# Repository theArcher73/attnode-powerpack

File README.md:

# AttNo.de-powerpack, a adapter-pcb to use 3.3-15V
 AddOn to use the [attnode](https://attno.de) v2/v3 with 3.3-15V DC

This small pcb allows to run the [attnode](https://attno.de) with an operating voltage between 3.3 and 15V, for example with a USB power supply, a LiPo or any other fixed voltage power supply.

It has the shape of the CR2032 battery clip and is soldered directly onto the [attnode](https://attno.de) instead of the CR2032-Clip.

Therefore, when ordering the pcb's, a smaller pcb thickness can be used if possible, I have had good experiences with 1.2mm.

The power supply can be either via the JST socket, or the two pads directly on the pcb. In this case, the JST socket must not be soldered.

The voltage source must provide at least 120 mA.

Update 26.05.2021: add a Voltage divider added to monitor the Vin with an ADC pin of the ATTiny. The resistance ratio must be determined based on Vin, here are some sample values. The voltage at the ADC pad should not exceed 2.1V.

Update 27.08.2021: add two Resistors 5K1 and Pads for external wiring to support USB-C

  Vin | Vmax |  R1 | R2
------|------|-----|----
3.7V | 4.2V | 1M | 1M
USB | 5.25V | 1M5 | 1M
9V | 11V | 6M8 | 1M5
12V | 15.4V | 10M | 1M5

Attention! Pay attention to the peak voltage, which is higher than the nominal voltage for many batteries!

More information can be found [here](https://www.attno.de/blog/2021-01-08).

 front  | back       
--------|--------
 | 

## Disclaimer

The documentation of the attno.de-powerpack is distributed in the hope that it will be useful, but WITHOUT ANY WARRANTY; without even the implied warranty of MERCHANTABILITY or FITNESS FOR A PARTICULAR PURPOSE.

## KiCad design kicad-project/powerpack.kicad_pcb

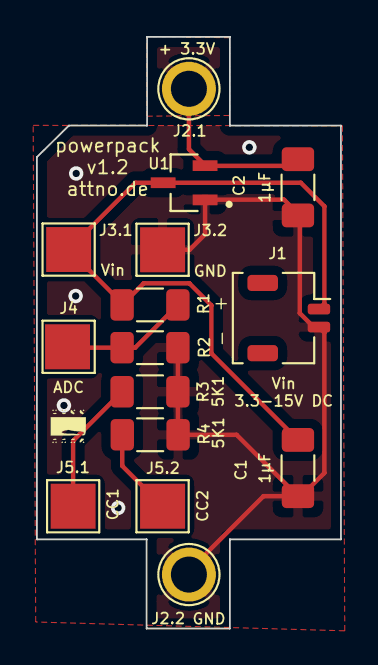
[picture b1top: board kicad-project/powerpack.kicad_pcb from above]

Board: 2 copper layers, 16.9 x 32.9 mm, 15 parts (0 on the bottom side), 6 nets.

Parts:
C1, C2: 1µF; C_1206_3216Metric_Pad1.33x1.80mm_HandSolder
J1: Power_in 3.3-15V; JST_SHL_SM02B-SHLS-TF_1x02-1MP_P1.00mm_Horizontal
J2.1: Vout +3.3V; TestPoint_Plated_Hole_D2.0mm
J2.2: Vout GND; TestPoint_Plated_Hole_D2.0mm
J3.1: Vin; TestPoint_Pad_2.5x2.5mm
J3.2: GND; TestPoint_Pad_2.5x2.5mm
J4: ADC; TestPoint_Pad_2.5x2.5mm
J5.1: CC1; TestPoint_Pad_2.5x2.5mm
J5.2: CC2; TestPoint_Pad_2.5x2.5mm
R1, R2: R; R_1206_3216Metric_Pad1.30x1.75mm_HandSolder
R3, R4: 5K1; R_1206_3216Metric_Pad1.30x1.75mm_HandSolder
U1: MCP1703T-3302E_CB; SOT95P255X145-3N

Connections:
+3V3: C2.1, J2.1.1, U1.2
GND: C1.2, C2.2, J1.2, J2.2.1, J3.2.1, R2.2, R3.2, R4.2, U1.1
unnamed: J4.1, R1.2, R2.1
unnamed: J5.1.1, R3.1
unnamed: J5.2.1, R4.1
VCC: C1.1, J1.1, J3.1.1, R1.1, U1.3

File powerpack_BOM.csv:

Reference;Quantity;Value;Bauteil;Footprint
C1, C2;2;1µF;Capacitor SMD 1206;Capacitor_SMD:C_1206_3216Metric_Pad1.33x1.80mm_HandSolder
J1;1;Power_in 3.3-15V;JST 2pin 1mm horizontal;Connector_JST:JST_SHL_SM02B-SHLS-TF_1x02-1MP_P1.00mm_Horizontal
U1;1;MCP1703T-3302E_CB;MCP 1703-3302E/CB;MCP1703T-3302E_CB:SOT95P255X145-3N

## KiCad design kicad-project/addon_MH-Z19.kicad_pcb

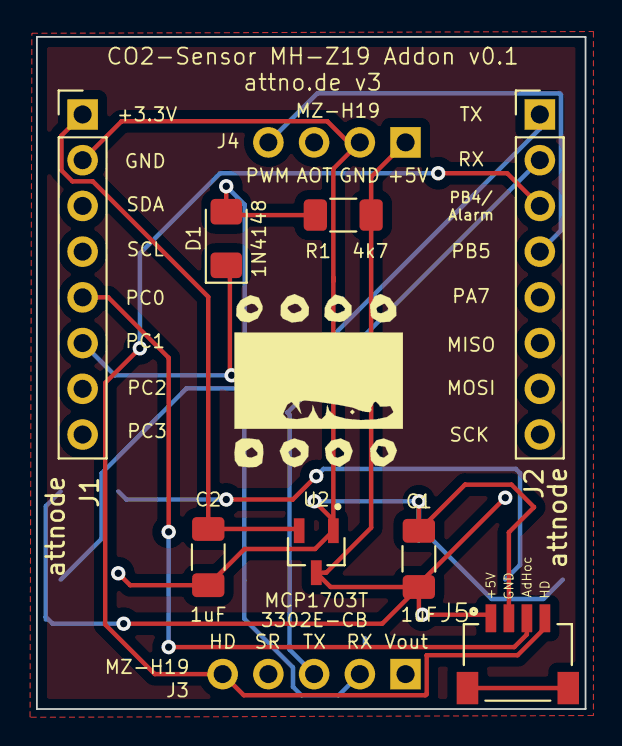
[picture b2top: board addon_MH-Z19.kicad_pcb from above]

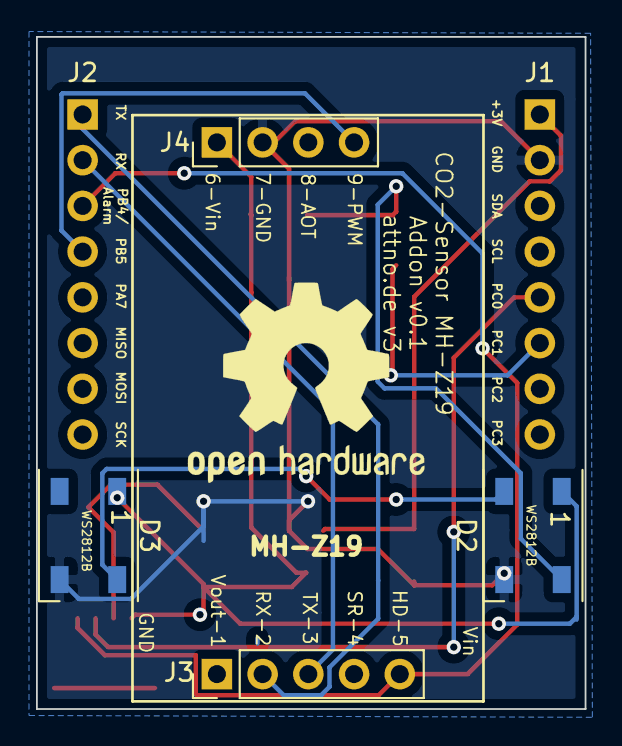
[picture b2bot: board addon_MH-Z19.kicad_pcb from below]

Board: 2 copper layers, 30.5 x 37.3 mm, 12 parts (4 on the bottom side), 12 nets.

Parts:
C1, C2: 1uF; C_1206_3216Metric_Pad1.33x1.80mm_HandSolder
D1: 1N4148; D_1206_3216Metric_Pad1.42x1.75mm_HandSolder
D2, D3: WS2812B; LED_WS2812B_PLCC4_5.0x5.0mm_P3.2mm
J1, J2: attnode; PinHeader_1x08_P2.54mm_Vertical
J3: MZ-H19; PinHeader_1x05_P2.54mm_Vertical
J4: MZ-H19; PinHeader_1x04_P2.54mm_Vertical
J5: SM04B-SRSS-TBT(LF)(SN); JST_SM04B-SRSS-TB(LF)(SN)
R1: 4k7; R_1206_3216Metric_Pad1.30x1.75mm_HandSolder
U2: MCP1703T; SOT95P255X145-3N

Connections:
+3V3: C2.1, J1.1, U2.2
+5V: C1.1, D2.1, D3.1, J4.1, J5.1, R1.1, U2.3
AdHoc: J1.5, J5.3
GND: C1.2, C2.2, D2.3, D3.3, J1.2, J4.2, J5.2, U2.1
HD: J2.3, J3.5, J5.4
unnamed: D1.2, D2.4, R1.2
unnamed: D2.2, D3.4
unnamed: J5.S1, J5.S2
PC1: D1.1, J1.6
PWM: J2.4, J4.4
RX: J2.2, J3.3
TX: J2.1, J3.2

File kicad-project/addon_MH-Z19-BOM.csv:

Reference;Quantity;Value;Description;Footprint
C1, C2;2;1µF;Capacitor SMD 1206;Capacitor_SMD:C_1206_3216Metric_Pad1.33x1.80mm_HandSolder
D1;1;1N4148;Diode SMD 1206;Diode_SMD:D_1206_3216Metric_Pad1.42x1.75mm_HandSolder
D2, D3;2;WS2812B;WS2812B;LED_SMD:LED_WS2812B_PLCC4_5.0x5.0mm_P3.2mm
J1;1;attnode J1;Pinheader Male 2,54mm 8 Pin;Connector_PinHeader_2.54mm:PinHeader_1x08_P2.54mm_Vertical
J2;1;attnode J2;Pinheader Male 2,54mm 8 Pin;Connector_PinHeader_2.54mm:PinHeader_1x08_P2.54mm_Vertical
J3;1;MZ-H19;Pinheader Male 2,54mm 5 Pin;Connector_PinHeader_2.54mm:PinHeader_1x05_P2.54mm_Vertical
J4;1;MZ-H19;Pinheader Male 2,54mm 4 Pin;Connector_PinHeader_2.54mm:PinHeader_1x04_P2.54mm_Vertical
J5;1;SM04B-SRSS-TBT(LF)(SN);JST 4pin Buchse horizontal;JST-SM04B-SRSS-TB_LF__SN:JST_SM04B-SRSS-TB(LF)(SN)
R1;1;4k7;Resistor SMD 1206;Resistor_SMD:R_1206_3216Metric_Pad1.30x1.75mm_HandSolder
U2;1;MCP1703T-3302E_CB;LDO MCP 1703T-3302E_CB;MCP1703T-3302E_CB:SOT95P255X145-3N

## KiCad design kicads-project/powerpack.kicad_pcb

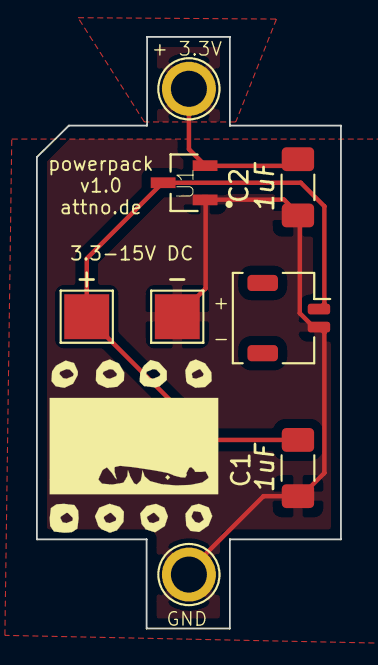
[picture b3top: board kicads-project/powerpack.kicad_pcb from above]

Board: 2 copper layers, 16.9 x 32.9 mm, 8 parts (0 on the bottom side), 3 nets.

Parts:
+: Vin 3.3V-15V; TestPoint_Pad_2.5x2.5mm
-: Vin GND; TestPoint_Pad_2.5x2.5mm
C1, C2: 1uF; C_1206_3216Metric_Pad1.33x1.80mm_HandSolder
J1: Power_in 3.3-15V; JST_SHL_SM02B-SHLS-TF_1x02-1MP_P1.00mm_Horizontal
J2.1: Vout +3.3V; TestPoint_Plated_Hole_D2.0mm
J2.2: Vout GND; TestPoint_Plated_Hole_D2.0mm
U1: MCP1703T-3302E_CB; SOT95P255X145-3N

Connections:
+3V3: C2.1, J2.1.1, U1.2
GND: -.1, C1.2, C2.2, J1.2, J2.2.1, U1.1
VCC: +.1, C1.1, J1.1, U1.3

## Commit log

2021-02-08 added readme and bugfix
2021-02-08 add BOM
2021-02-08 add link to powerpack
2021-02-08 cleanup
2021-05-26 update Silk and folder
2021-05-30 add disclaimer
2021-05-30 update disclaimer
2021-08-27 Added Support USB-C
